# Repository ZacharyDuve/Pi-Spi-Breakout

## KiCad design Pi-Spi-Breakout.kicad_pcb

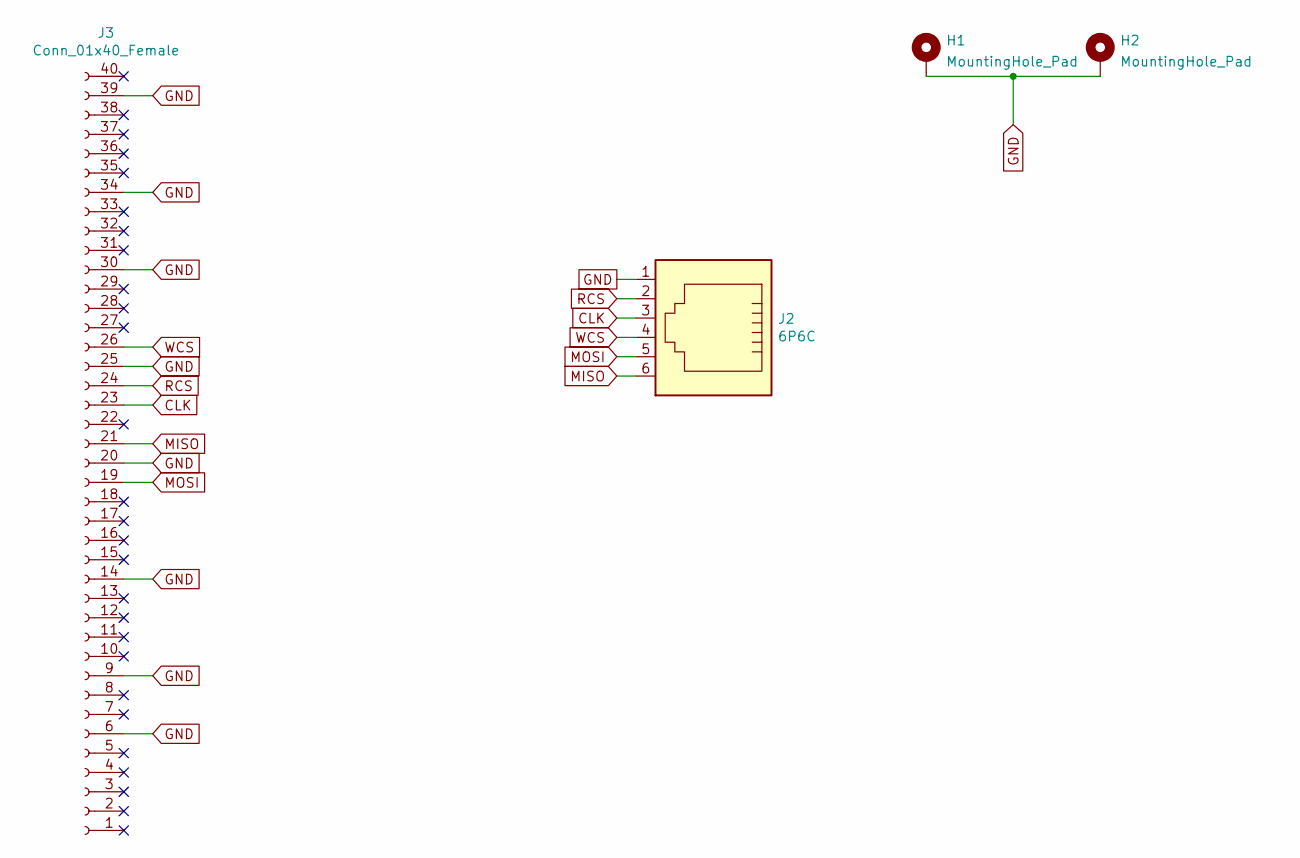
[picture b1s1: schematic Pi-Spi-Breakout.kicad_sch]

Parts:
H1, H2: MountingHole_Pad; MountingHole_2.7mm_Pad
J2: 6P6C; 6P6C-MTJ-660x1
J3: Conn_01x40_Female; PinSocket_2x20_P2.54mm_Vertical

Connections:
CLK: J2.3, J3.23
GND: H1.1, H2.1, J2.1, J3.6, J3.9, J3.14, J3.20, J3.25, J3.30, J3.34, J3.39
MISO: J2.6, J3.21
MOSI: J2.5, J3.19
RCS: J2.2, J3.24
WCS: J2.4, J3.26

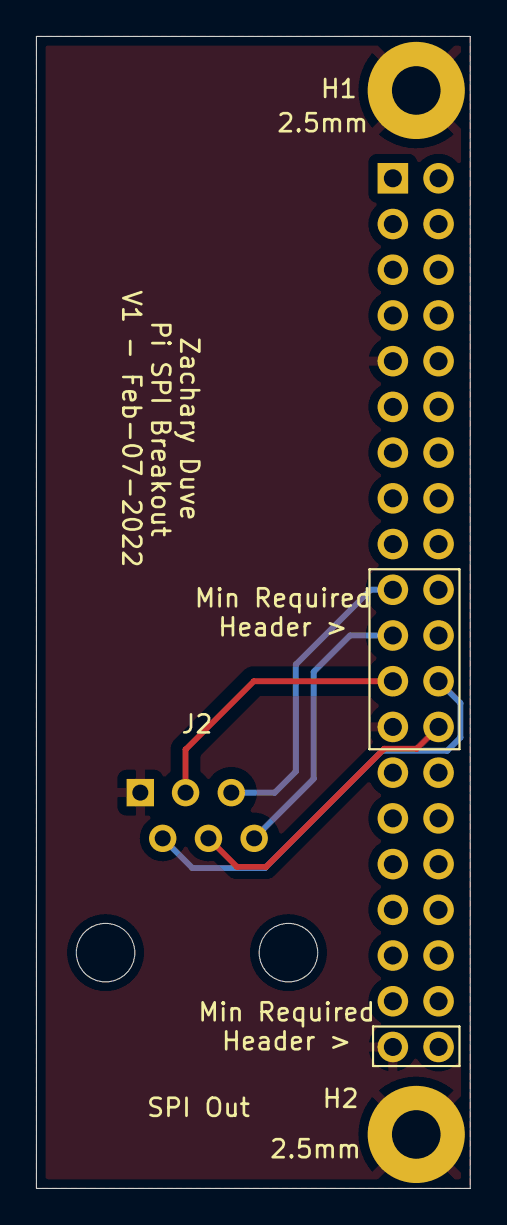
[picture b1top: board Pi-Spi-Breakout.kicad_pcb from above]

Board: 2 copper layers, 24.1 x 64.0 mm, 4 parts (1 on the bottom side), 6 nets.

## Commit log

2022-02-17 V1 sent to fab. Contains breakout of SPI pins on pi to a 6P6C jack
